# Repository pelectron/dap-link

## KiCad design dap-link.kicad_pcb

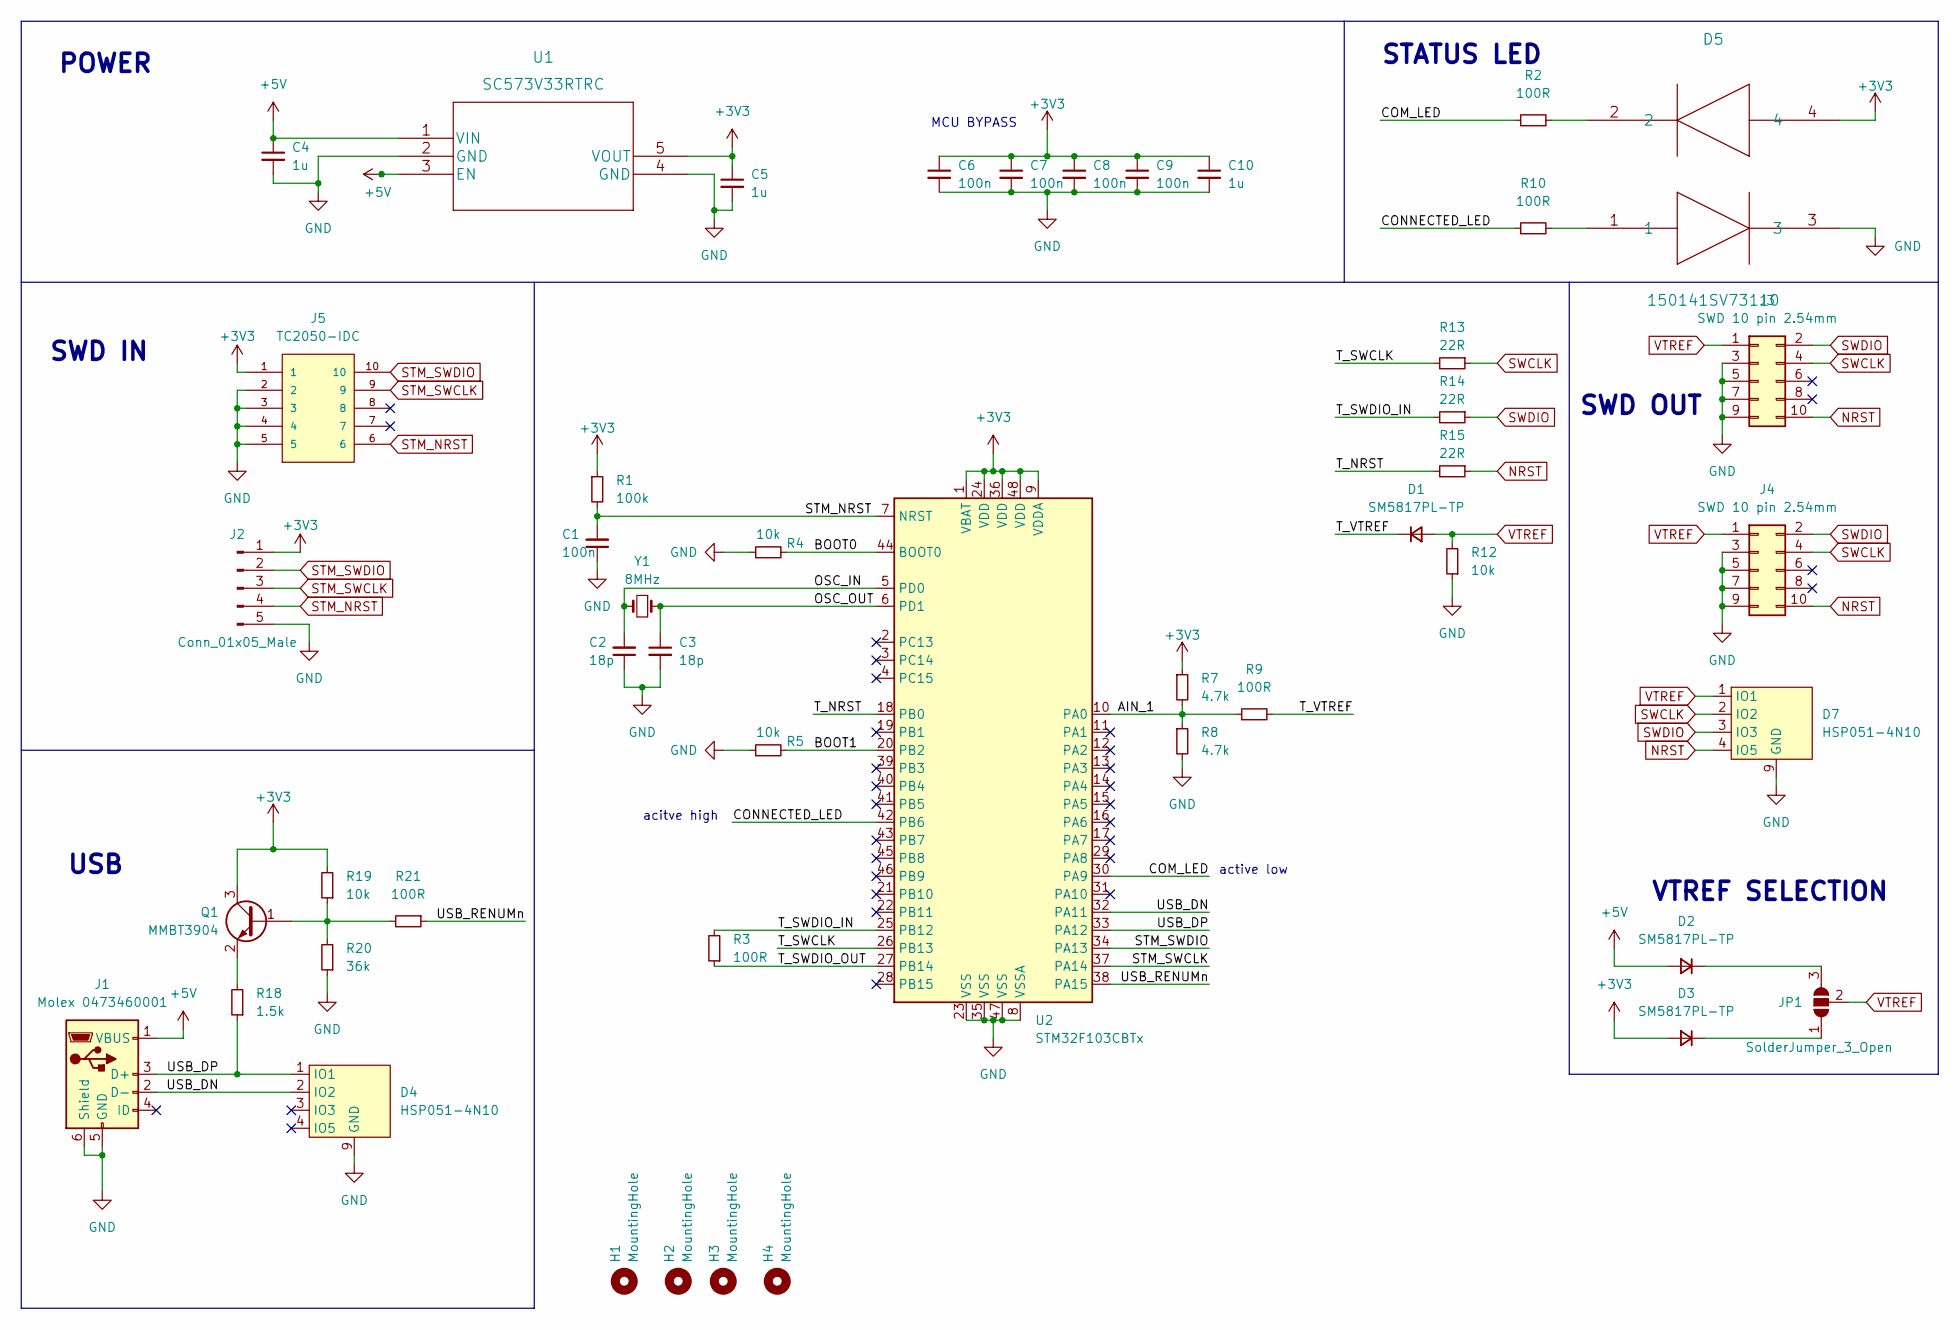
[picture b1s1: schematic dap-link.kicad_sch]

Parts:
C1, C6, C7, C8, C9: 100n; C_0603_1608Metric
C2, C3: 18p; C_0603_1608Metric
C4, C5, C10: 1u; C_0603_1608Metric
D1, D2, D3: SM5817PL-TP; D_SOD-123
D4, D7: HSP051-4N10; UQFN1.9x1_10L
D5: 150141SV73110
H1, H2, H3, H4: MountingHole; MountingHole_3.2mm_M3
J1: Molex 0473460001; Molex_0473460001; Manufacturer PN 0473460001
J2: Conn_01x05_Male; SWD_SOLDER
J3: SWD 10 pin 2.54mm; PinHeader_2x05_P2.54mm_Vertical_SMD
J4: SWD 10 pin 2.54mm; GBED204-0579B001C1AD
J5: TC2050-IDC; TAG-CONNECT_TC2050-IDC; PARTREV A
JP1: SolderJumper_3_Open; SolderJumper-3_P2.0mm_Open_TrianglePad1.0x1.5mm
Q1: MMBT3904; TSOT-23
R1: 100k; R_0603_1608Metric
R2, R3, R9, R10, R21: 100R; R_0603_1608Metric
R4, R5, R12, R19: 10k; R_0603_1608Metric
R7, R8: 4.7k; R_0603_1608Metric
R13, R14, R15: 22R; R_0603_1608Metric
R18: 1.5k; R_0603_1608Metric
R20: 36k; R_0603_1608Metric
U1: SC573V33RTRC
U2: STM32F103CBTx; LQFP-48_7x7mm_P0.5mm
Y1: 8MHz; ECS-023G

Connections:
+3V3: C5.1, C6.1, C7.1, C8.1, C9.1, C10.1, D3.2 (A), D5.4, J2.1, J5.1, Q1.3 (C), R1.1, R7.1, R19.2, U1.5 (VOUT), U2.1 (VBAT), U2.9 (VDDA), U2.24 (VDD), U2.36 (VDD), U2.48 (VDD)
+5V: C4.1, D2.2 (A), J1.1 (VBUS), U1.1 (VIN), U1.3 (EN)
/AIN_1: R7.2, R8.1, R9.1, U2.10 (PA0)
/BOOT0: R4.2, U2.44 (BOOT0)
/BOOT1: R5.2, U2.20 (PB2)
/COM_LED: R2.1, U2.30 (PA9)
/CONNECTED_LED: R10.1, U2.42 (PB6)
/OSC_IN: C2.2, U2.5 (PD0), Y1.2
/OSC_OUT: C3.1, U2.6 (PD1), Y1.1
/T_NRST: R15.2, U2.18 (PB0)
/T_SWCLK: R13.2, U2.26 (PB13)
/T_SWDIO_IN: R3.2, R14.2, U2.25 (PB12)
/T_SWDIO_OUT: R3.1, U2.27 (PB14)
/T_VTREF: D1.1 (K), R9.2
/USB_DN: D4.2 (IO2), J1.2 (D-), U2.32 (PA11)
/USB_DP: D4.1 (IO1), J1.3 (D+), R18.1, U2.33 (PA12)
/USB_RENUMn: R21.1, U2.38 (PA15)
GND: C1.1, C2.1, C3.2, C4.2, C5.2, C6.2, C7.2, C8.2, C9.2, C10.2, D4.9 (GND), D5.3, D7.9 (GND), J1.5 (GND), J1.6 (Shield), J2.5, J3.3, J3.5, J3.7, J3.9, J4.3, J4.5, J4.7, J4.9, J5.2, J5.3, J5.4, J5.5, R4.1, R5.1, R8.2, R12.1, R20.1, U1.2 (GND), U1.4 (GND), U2.8 (VSSA), U2.23 (VSS), U2.35 (VSS), U2.47 (VSS)
NRST: D7.4 (IO5), J3.10, J4.10, R15.1
unnamed: D2.1 (K), JP1.3 (B)
unnamed: D3.1 (K), JP1.1 (A)
unnamed: D5.1, R10.2
unnamed: D5.2, R2.2
unnamed: Q1.1 (B), R19.1, R20.2, R21.2
unnamed: Q1.2 (E), R18.2
STM_NRST: C1.2, J2.4, J5.6, R1.2, U2.7 (NRST)
STM_SWCLK: J2.3, J5.9, U2.37 (PA14)
STM_SWDIO: J2.2, J5.10, U2.34 (PA13)
SWCLK: D7.2 (IO2), J3.4, J4.4, R13.1
SWDIO: D7.3 (IO3), J3.2, J4.2, R14.1
VTREF: D1.2 (A), D7.1 (IO1), J3.1, J4.1, JP1.2 (C), R12.2

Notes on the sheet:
STATUS LED
active low
POWER
USB
SWD IN
SWD OUT
MCU BYPASS
acitve high
VTREF SELECTION

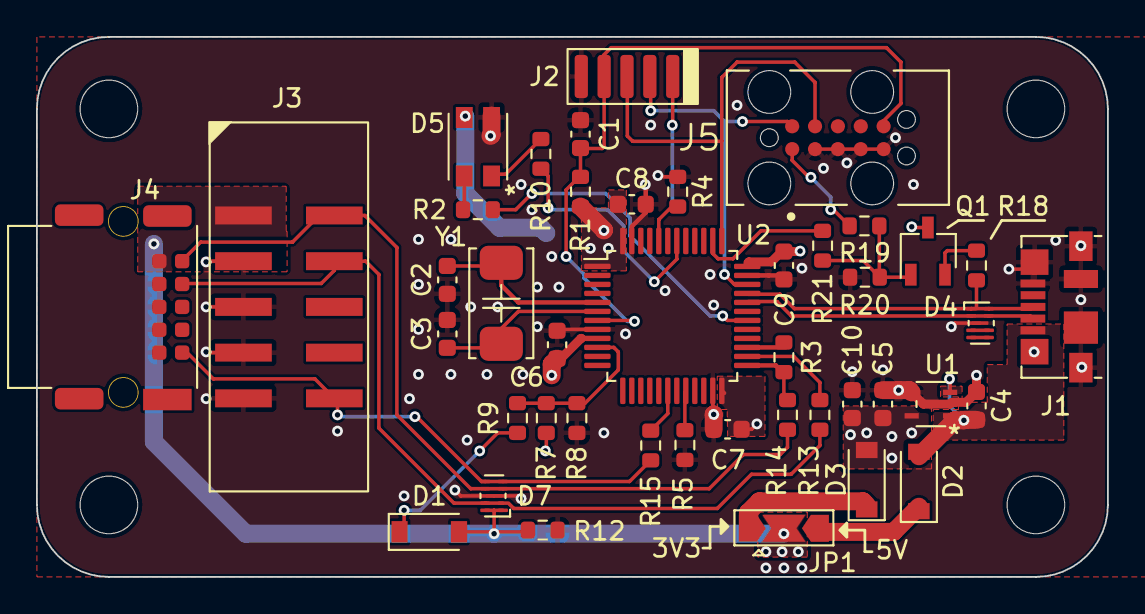
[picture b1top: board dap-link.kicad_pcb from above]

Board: 4 copper layers, 59.5 x 30.0 mm, 47 parts (0 on the bottom side), 31 nets.

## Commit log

2023-01-22 added gitignore
2023-01-23 case v1
2023-02-04 changed 1.27mm swd out connector to horizontal orientation
2023-02-04 added DAPLink firmware as submodule
2023-02-04 updated build script

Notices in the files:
parts and their libraries:
Copyright 2021 Accelerated Designs. All rights reserved.
